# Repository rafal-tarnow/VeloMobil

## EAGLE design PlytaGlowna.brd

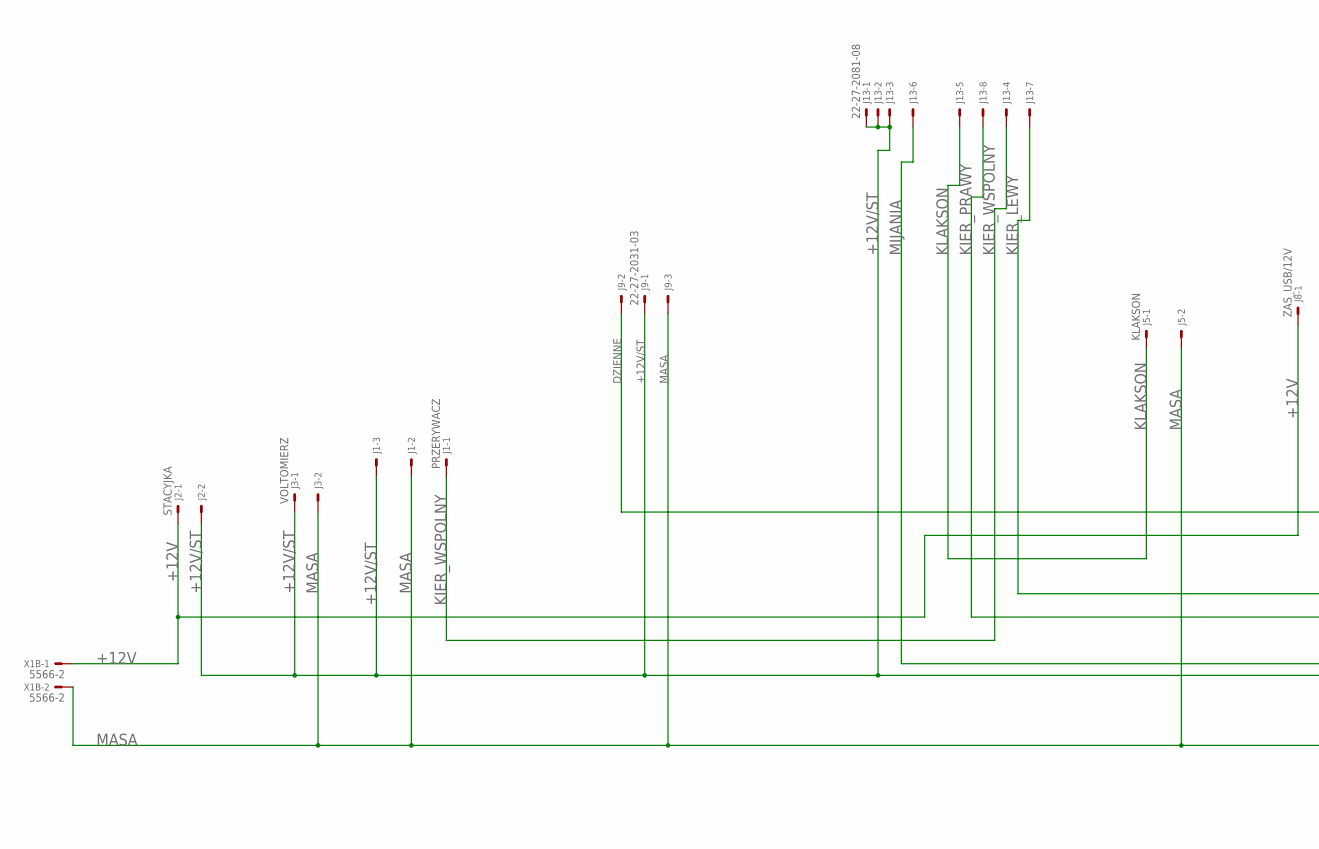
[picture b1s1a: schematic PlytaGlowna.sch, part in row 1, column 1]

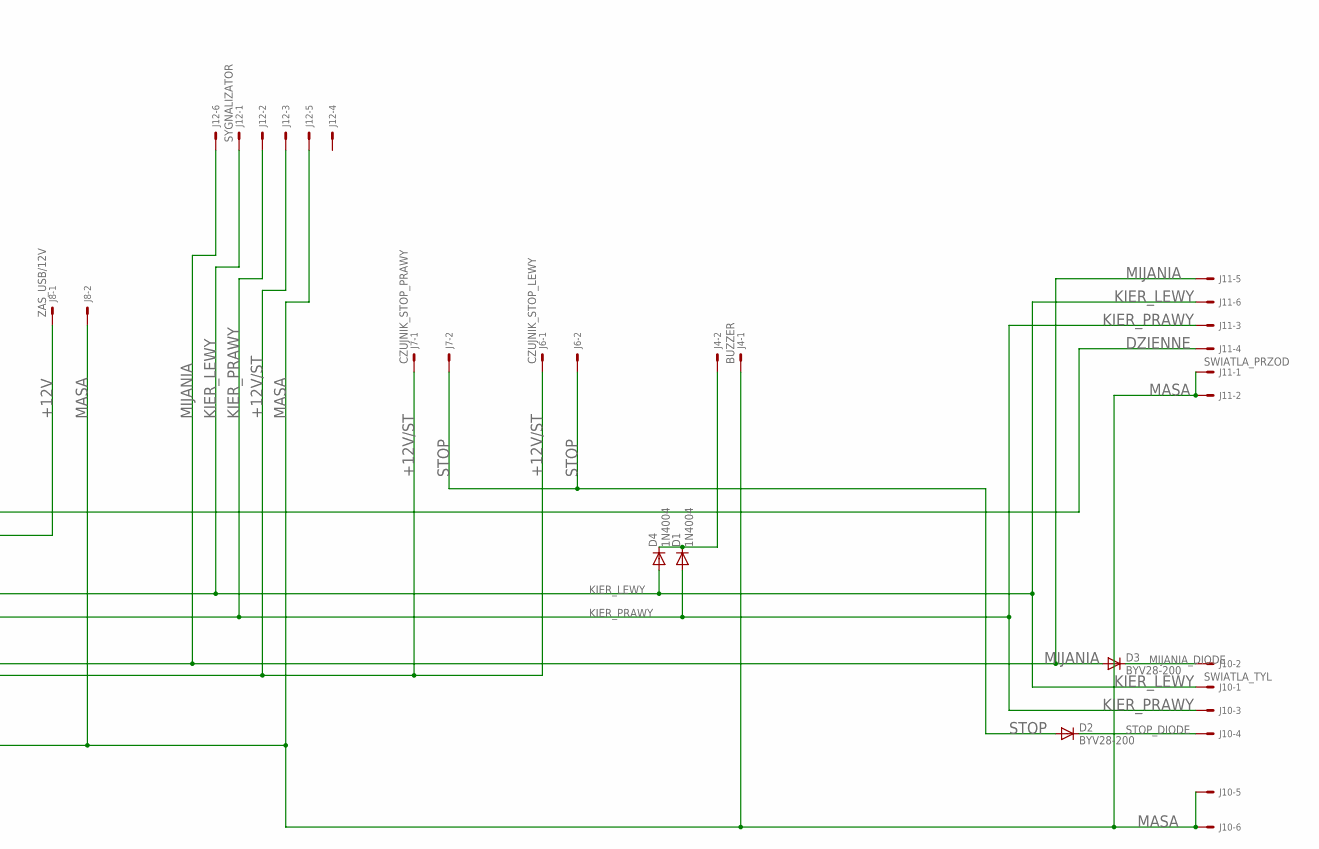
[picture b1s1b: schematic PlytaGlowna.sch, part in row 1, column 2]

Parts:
D1, D4: 1N4004; DO41-10
D2, D3: BYV28-200; SOD64-10
J1: PRZERYWACZ; 6410-03
J2: STACYJKA; 6410-02
J3: VOLTOMIERZ; 6410-02
J4: BUZZER; 6410-02
J5: KLAKSON; 6410-02
J6: CZUJNIK_STOP_LEWY; 6410-02
J7: CZUJNIK_STOP_PRAWY; 6410-02
J8: ZAS_USB/12V; 6410-02
J9: 22-27-2031-03; 6410-03
J10: SWIATLA_TYL; 6410-06
J11: SWIATLA_PRZOD; 6410-06
J12: SYGNALIZATOR; 6410-06
J13: 22-27-2081-08; 6410-08
X1B: 5566-2

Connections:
+12V: J2.1, J8.1, X1B.1
+12V/ST: J1.3, J2.2, J3.1, J6.1, J7.1, J9.1, J12.3, J13.1, J13.2, J13.3
DZIENNE: J9.2, J11.4
KIER_LEWY: D4.A, J10.1, J11.6, J12.1, J13.7
KIER_PRAWY: D1.A, J10.3, J11.3, J12.2, J13.8
KIER_WSPOLNY: J1.1, J13.4
KLAKSON: J5.1, J13.5
MASA: J1.2, J3.2, J4.1, J5.2, J8.2, J9.3, J10.5, J10.6, J11.1, J11.2, J12.5, X1B.2
MIJANIA: D3.A, J11.5, J12.6, J13.6
MIJANIA_DIODE: D3.C, J10.2
unnamed: D1.C, D4.C, J4.2
STOP: D2.A, J6.2, J7.2
STOP_DIODE: D2.C, J10.4

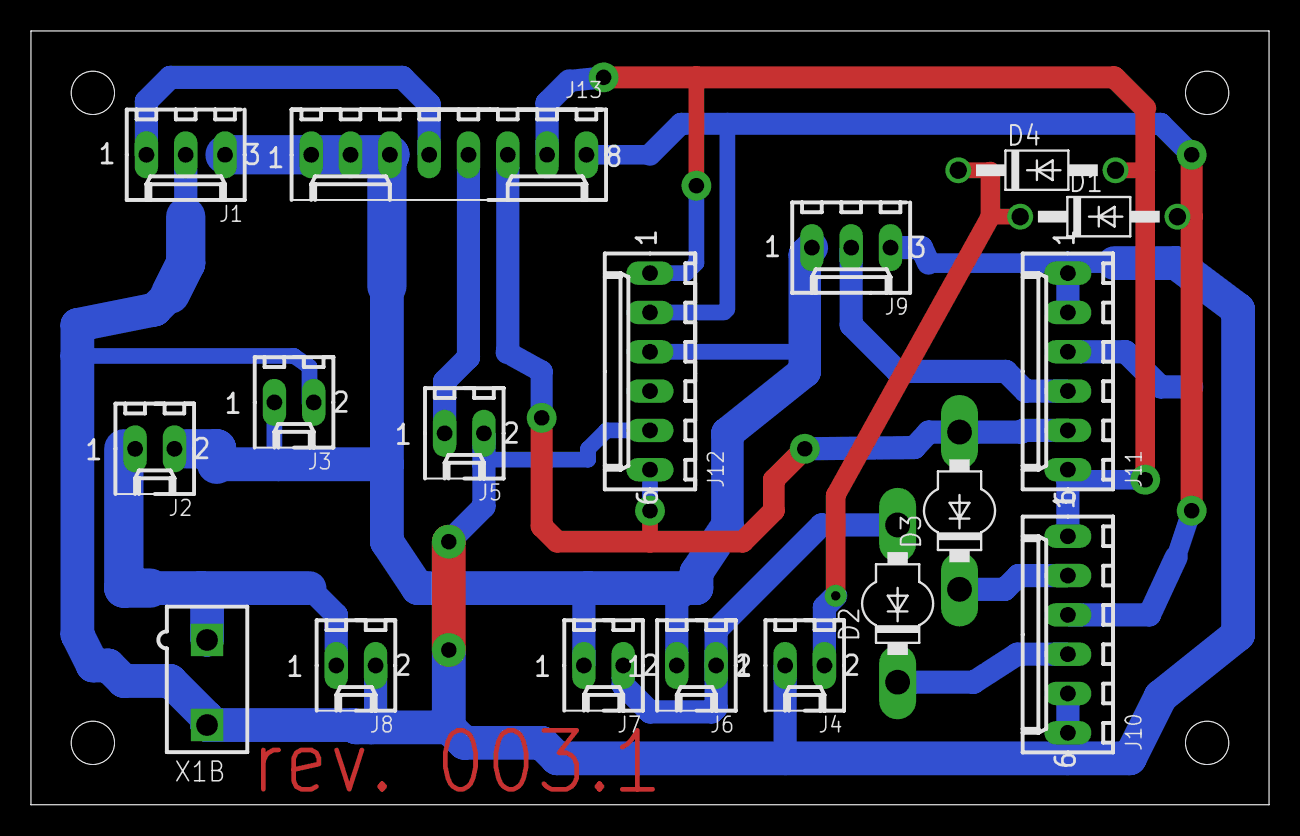
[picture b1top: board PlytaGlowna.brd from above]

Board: 2 copper layers, 80.0 x 50.0 mm, 18 parts (0 on the bottom side), 13 nets.

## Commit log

2017-06-24 rev.001 , pierwsza wyprodukowana wersja
2017-06-24 druga wyprodukowana plytka
2018-03-02 czesc zmian do wersji 3
2018-03-12 temporary changes
2018-03-13 rev.003 RC1
2018-03-13 rev.003 RC2
2018-03-13 poprawki diod, ver.003 RC3
2018-03-26 poprawki routingu sciezek, ver.003 RC4
2019-03-20 poprawki tylko grubosci sciezek, brak zmian schematu, rev.003.1 RC5
